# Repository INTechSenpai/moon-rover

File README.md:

# INTech Senpaï vous présente son dernier robot : [le moon rover !](https://intechsenpai.github.io/moon-rover/)

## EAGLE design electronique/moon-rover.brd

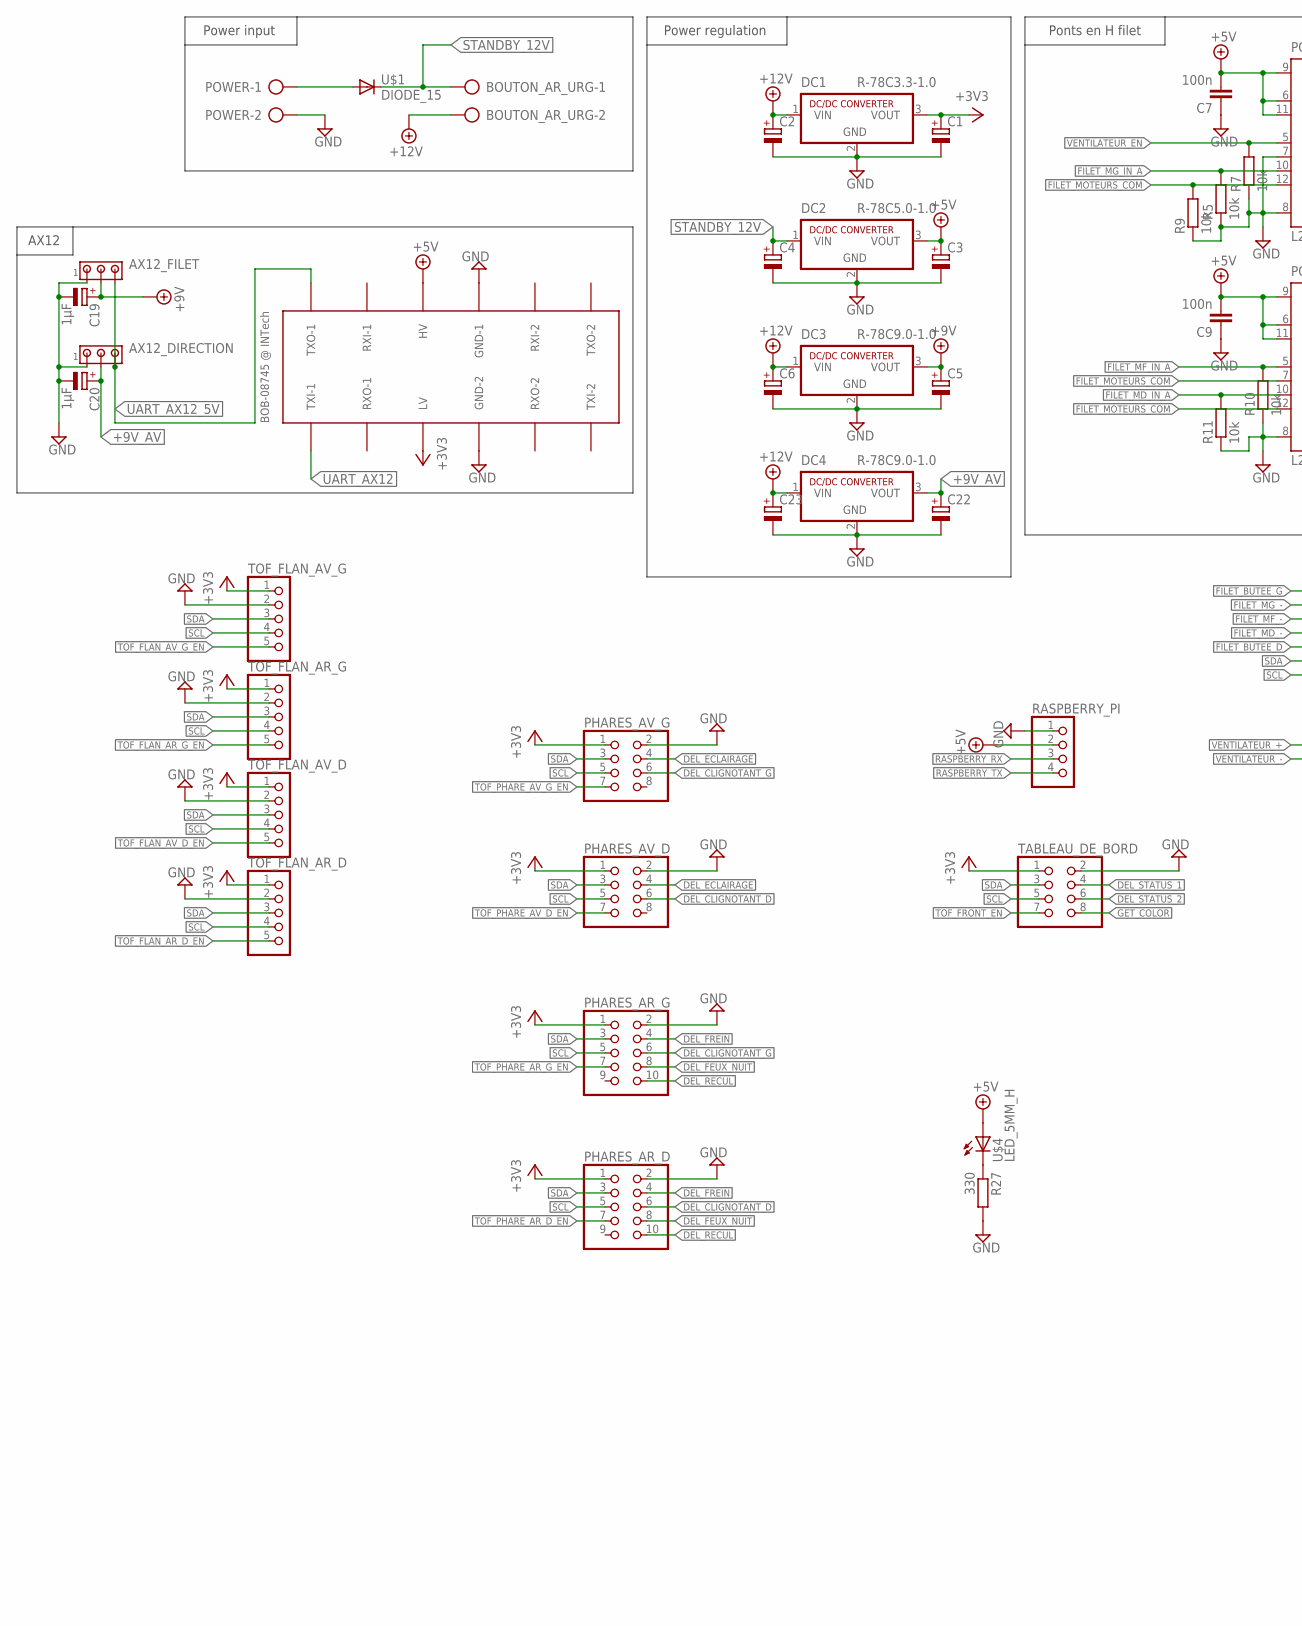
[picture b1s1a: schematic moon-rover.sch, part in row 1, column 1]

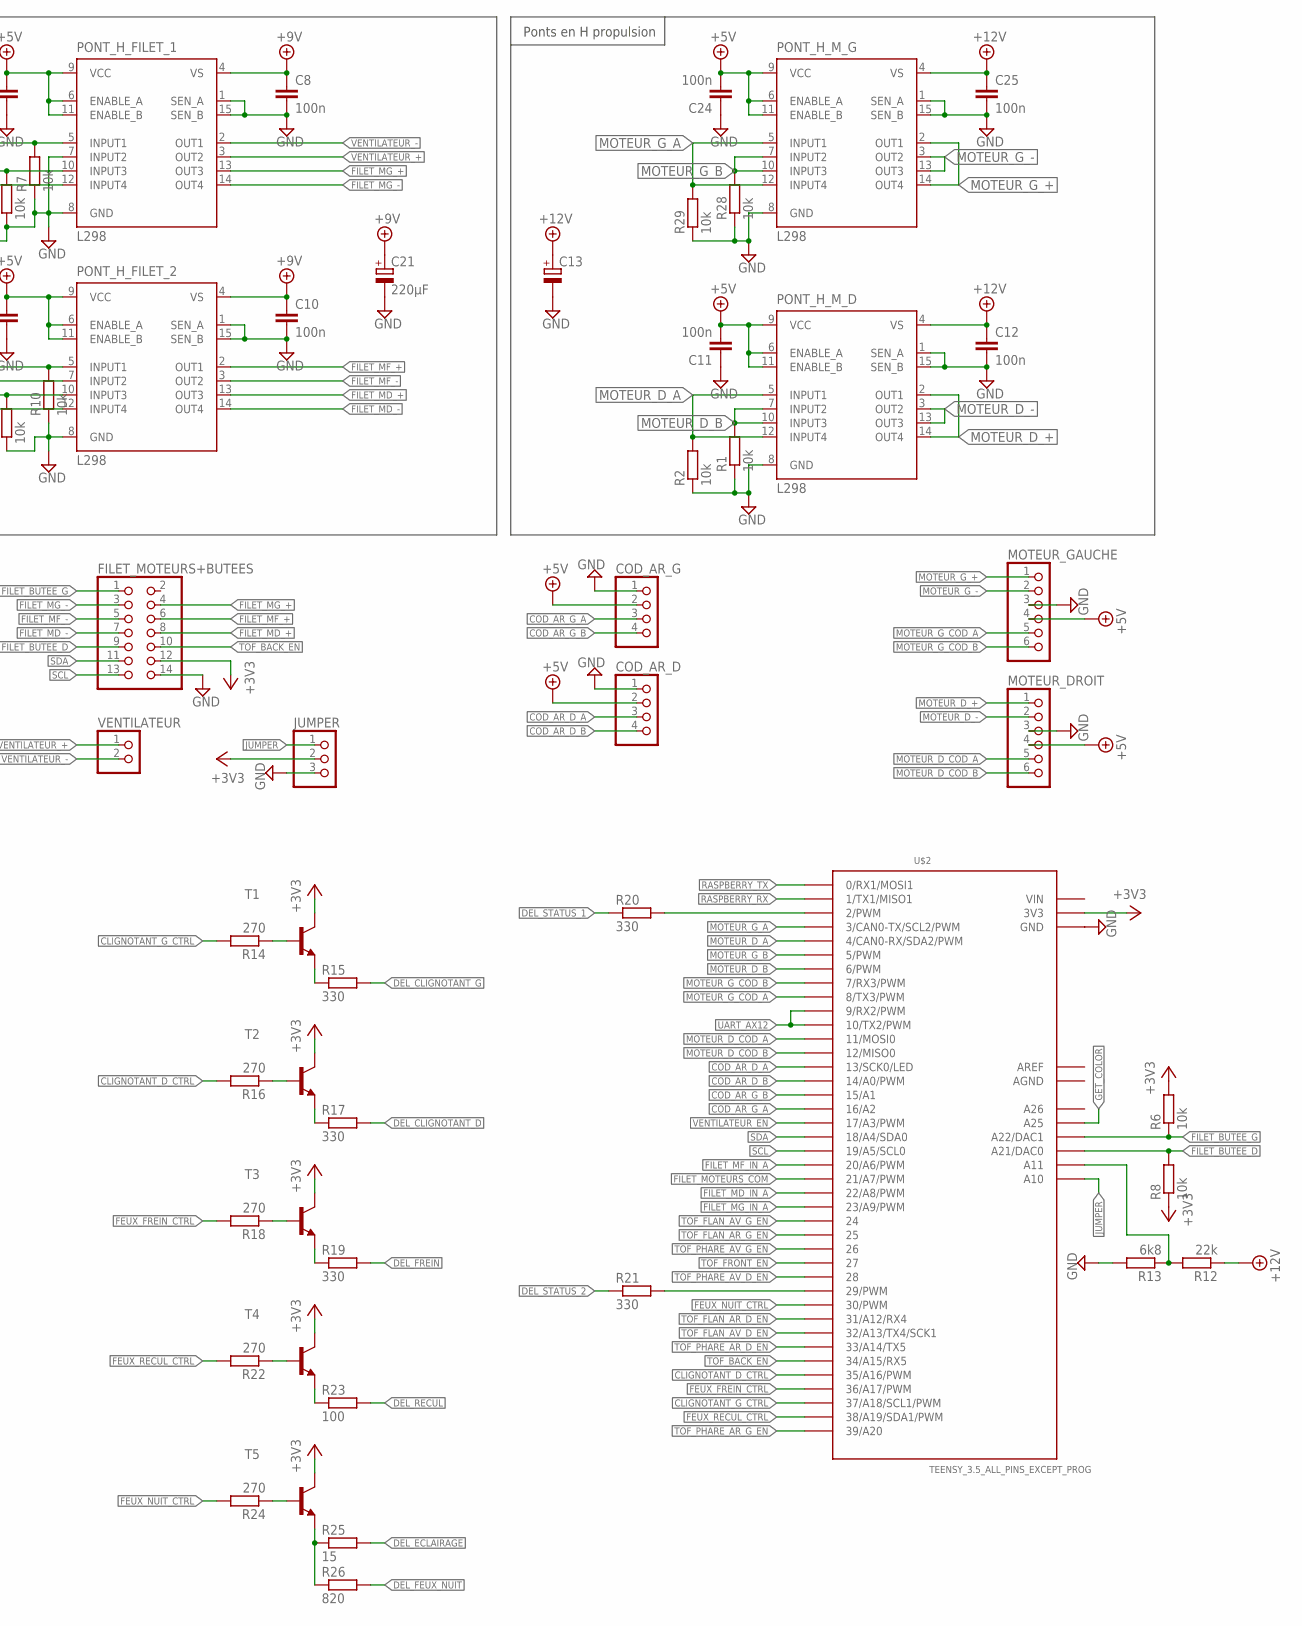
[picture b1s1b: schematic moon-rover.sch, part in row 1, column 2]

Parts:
AX12_DIRECTION, AX12_FILET: MTA03-100; 10X03MTA
BOUTON_AR_URG: AK300/2
C1, C2, C3, C4, C5, C6, C22, C23: CPOL-EUE2.5-6; E2,5-6
C7, C8, C9, C10, C11, C12, C24, C25: 100n; C050-024X044
C13: CPOL-EUE5-13; E5-13
C19, C20: 1µF; E2,5-5
C21: 220µF; E3,5-8
COD_AR_D: PINHD-1X4/90; 1X04/90
COD_AR_G: PINHD-1X4/90; 1X04/90
DC1: R-78C3.3-1.0; SIP3
DC2: R-78C5.0-1.0; SIP3
DC3, DC4: R-78C9.0-1.0; SIP3
FILET_MOTEURS+BUTEES: PINHD-2X7; 2X07
JUMPER: PINHD-1X3/90; 1X03/90
MOTEUR_DROIT: PINHD-1X6/90; 1X06/90
MOTEUR_GAUCHE: PINHD-1X6/90; 1X06/90
PHARES_AR_D: PINHD-2X5; 2X05
PHARES_AR_G: PINHD-2X5; 2X05
PHARES_AV_D: PINHD-2X4; 2X04
PHARES_AV_G: PINHD-2X4; 2X04
PONT_H_FILET_1, PONT_H_FILET_2: L298; MULTIWATT-15
PONT_H_M_D: L298; MULTIWATT-15; MPN L298N
PONT_H_M_G: L298; MULTIWATT-15; MPN L298N
POWER: AK300/2
R1, R2, R5, R6, R7, R8, R9, R10, R11, R28, R29: 10k; 0204/7
R12: 22k; 0204/7
R13: 6k8; 0204/7
R14, R16, R18, R22: 270; 0204/7
R15, R17, R19, R21: 330; 0207/2V
R20, R27: 330; 0204/7
R23: 100; 0207/2V
R24: 270; 0207/2V
R25: 15; 0207/2V
R26: 820; 0207/2V
RASPBERRY_PI: PINHD-1X4/90; 1X04/90
T1, T2, T3, T4, T5: BC237-NPN-TO92-CBE; TO92-CBE
TABLEAU_DE_BORD: PINHD-2X4; 2X04
TOF_FLAN_AR_D: PINHD-1X5; 1X05
TOF_FLAN_AR_G: PINHD-1X5; 1X05
TOF_FLAN_AV_D: PINHD-1X5; 1X05
TOF_FLAN_AV_G: PINHD-1X5; 1X05
U$1: DIODE_15; DO201-15
U$2: TEENSY_3.5_ALL_PINS_EXCEPT_PROG
U$3: BOB-08745
U$4: LED_5MM_H; Q62902-B155
VENTILATEUR: PINHD-1X2/90; 1X02/90

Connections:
+3V3: C1.+, DC1.3 (VOUT), FILET_MOTEURS+BUTEES.12, JUMPER.2, PHARES_AR_D.1, PHARES_AR_G.1, PHARES_AV_D.1, PHARES_AV_G.1, R6.2, R8.1, T1.C, T2.C, T3.C, T4.C, T5.C, TABLEAU_DE_BORD.1, TOF_FLAN_AR_D.1, TOF_FLAN_AR_G.1, TOF_FLAN_AV_D.1, TOF_FLAN_AV_G.1, U$2.3.3V (3V3), U$2.3.3V3 (3V3), U$3.LV
+5V: C3.+, C7.2, C9.2, C11.2, C24.2, COD_AR_D.2, COD_AR_G.2, DC2.3 (VOUT), MOTEUR_DROIT.4, MOTEUR_GAUCHE.4, PONT_H_FILET_1.6 (ENABLE_A), PONT_H_FILET_1.9 (VCC), PONT_H_FILET_1.11 (ENABLE_B), PONT_H_FILET_2.6 (ENABLE_A), PONT_H_FILET_2.9 (VCC), PONT_H_FILET_2.11 (ENABLE_B), PONT_H_M_D.6 (ENABLE_A), PONT_H_M_D.9 (VCC), PONT_H_M_D.11 (ENABLE_B), PONT_H_M_G.6 (ENABLE_A), PONT_H_M_G.9 (VCC), PONT_H_M_G.11 (ENABLE_B), RASPBERRY_PI.2, U$3.HV, U$4.A+
+9V: AX12_FILET.2, C5.+, C8.1, C10.1, C19.+, C21.+, DC3.3 (VOUT), PONT_H_FILET_1.4 (VS), PONT_H_FILET_2.4 (VS)
+9V_AV: AX12_DIRECTION.2, C20.+, C22.+, DC4.3 (VOUT)
+12V: BOUTON_AR_URG.2, C2.+, C6.+, C12.1, C13.+, C23.+, C25.1, DC1.1 (VIN), DC3.1 (VIN), DC4.1 (VIN), PONT_H_M_D.4 (VS), PONT_H_M_G.4 (VS), R12.1
AGND: U$2.AGND
AREF: U$2.AREF
CLIGNOTANT_D_CTRL: R16.2, U$2.35/A16 (35/A16/PWM)
CLIGNOTANT_G_CTRL: R14.2, U$2.37/A18 (37/A18/SCL1/PWM)
COD_AR_D_A: COD_AR_D.3, U$2.13 (13/SCK0/LED)
COD_AR_D_B: COD_AR_D.4, U$2.14/A0 (14/A0/PWM)
COD_AR_G_A: COD_AR_G.3, U$2.16/A2
COD_AR_G_B: COD_AR_G.4, U$2.15/A1
DEL_CLIGNOTANT_D: PHARES_AR_D.6, PHARES_AV_D.6, R17.2
DEL_CLIGNOTANT_G: PHARES_AR_G.6, PHARES_AV_G.6, R15.2
DEL_ECLAIRAGE: PHARES_AV_D.4, PHARES_AV_G.4, R25.2
DEL_FEUX_NUIT: PHARES_AR_D.8, PHARES_AR_G.8, R26.2
DEL_FREIN: PHARES_AR_D.4, PHARES_AR_G.4, R19.2
DEL_RECUL: PHARES_AR_D.10, PHARES_AR_G.10, R23.2
DEL_STATUS_1: R20.1, TABLEAU_DE_BORD.4
DEL_STATUS_2: R21.1, TABLEAU_DE_BORD.6
FEUX_FREIN_CTRL: R18.2, U$2.36/A17 (36/A17/PWM)
FEUX_NUIT_CTRL: R24.2, U$2.30 (30/PWM)
FEUX_RECUL_CTRL: R22.2, U$2.38/A19 (38/A19/SDA1/PWM)
FILET_BUTEE_D: FILET_MOTEURS+BUTEES.9, R8.2, U$2.A21 (A21/DAC0)
FILET_BUTEE_G: FILET_MOTEURS+BUTEES.1, R6.1, U$2.A22 (A22/DAC1)
FILET_MD_+: FILET_MOTEURS+BUTEES.8, PONT_H_FILET_2.13 (OUT3)
FILET_MD_-: FILET_MOTEURS+BUTEES.7, PONT_H_FILET_2.14 (OUT4)
FILET_MD_IN_A: PONT_H_FILET_2.10 (INPUT3), R11.2, U$2.22/A8 (22/A8/PWM)
FILET_MF_+: FILET_MOTEURS+BUTEES.6, PONT_H_FILET_2.2 (OUT1)
FILET_MF_-: FILET_MOTEURS+BUTEES.5, PONT_H_FILET_2.3 (OUT2)
FILET_MF_IN_A: PONT_H_FILET_2.5 (INPUT1), R10.2, U$2.20/A6 (20/A6/PWM)
FILET_MG_+: FILET_MOTEURS+BUTEES.4, PONT_H_FILET_1.13 (OUT3)
FILET_MG_-: FILET_MOTEURS+BUTEES.3, PONT_H_FILET_1.14 (OUT4)
FILET_MG_IN_A: PONT_H_FILET_1.10 (INPUT3), R5.2, U$2.23/A9 (23/A9/PWM)
FILET_MOTEURS_COM: PONT_H_FILET_1.12 (INPUT4), PONT_H_FILET_2.7 (INPUT2), PONT_H_FILET_2.12 (INPUT4), R9.2, U$2.21/A7 (21/A7/PWM)
GET_COLOR: TABLEAU_DE_BORD.8, U$2.A25
GND: AX12_DIRECTION.1, AX12_FILET.1, C1.-, C2.-, C3.-, C4.-, C5.-, C6.-, C7.1, C8.2, C9.1, C10.2, C11.1, C12.2, C13.-, C19.-, C20.-, C21.-, C22.-, C23.-, C24.1, C25.2, COD_AR_D.1, COD_AR_G.1, DC1.2 (GND), DC2.2 (GND), DC3.2 (GND), DC4.2 (GND), FILET_MOTEURS+BUTEES.14, JUMPER.3, MOTEUR_DROIT.3, MOTEUR_GAUCHE.3, PHARES_AR_D.2, PHARES_AR_G.2, PHARES_AV_D.2, PHARES_AV_G.2, PONT_H_FILET_1.1 (SEN_A), PONT_H_FILET_1.7 (INPUT2), PONT_H_FILET_1.8 (GND), PONT_H_FILET_1.15 (SEN_B), PONT_H_FILET_2.1 (SEN_A), PONT_H_FILET_2.8 (GND), PONT_H_FILET_2.15 (SEN_B), PONT_H_M_D.1 (SEN_A), PONT_H_M_D.8 (GND), PONT_H_M_D.15 (SEN_B), PONT_H_M_G.1 (SEN_A), PONT_H_M_G.8 (GND), PONT_H_M_G.15 (SEN_B), POWER.2, R1.1, R2.1, R5.1, R7.1, R9.1, R10.1, R11.1, R13.2, R27.2, R28.1, R29.1, RASPBERRY_PI.1, TABLEAU_DE_BORD.2, TOF_FLAN_AR_D.2, TOF_FLAN_AR_G.2, TOF_FLAN_AV_D.2, TOF_FLAN_AV_G.2, U$2.GND, U$2.GND1 (GND), U$2.GND3 (GND), U$2.GND4 (GND), U$3.GND-1, U$3.GND-2
JUMPER: JUMPER.1, U$2.A10
MOTEUR_D_+: MOTEUR_DROIT.1, PONT_H_M_D.2 (OUT1), PONT_H_M_D.14 (OUT4)
MOTEUR_D_-: MOTEUR_DROIT.2, PONT_H_M_D.3 (OUT2), PONT_H_M_D.13 (OUT3)
MOTEUR_D_A: PONT_H_M_D.5 (INPUT1), PONT_H_M_D.12 (INPUT4), R2.2, U$2.4 (4/CAN0-RX/SDA2/PWM)
MOTEUR_D_B: PONT_H_M_D.7 (INPUT2), PONT_H_M_D.10 (INPUT3), R1.2, U$2.6 (6/PWM)
MOTEUR_D_COD_A: MOTEUR_DROIT.5, U$2.11 (11/MOSI0)
MOTEUR_D_COD_B: MOTEUR_DROIT.6, U$2.12 (12/MISO0)
MOTEUR_G_+: MOTEUR_GAUCHE.1, PONT_H_M_G.2 (OUT1), PONT_H_M_G.14 (OUT4)
MOTEUR_G_-: MOTEUR_GAUCHE.2, PONT_H_M_G.3 (OUT2), PONT_H_M_G.13 (OUT3)
MOTEUR_G_A: PONT_H_M_G.5 (INPUT1), PONT_H_M_G.12 (INPUT4), R29.2, U$2.3 (3/CAN0-TX/SCL2/PWM)
MOTEUR_G_B: PONT_H_M_G.7 (INPUT2), PONT_H_M_G.10 (INPUT3), R28.2, U$2.5 (5/PWM)
MOTEUR_G_COD_A: MOTEUR_GAUCHE.5, U$2.8 (8/TX3/PWM)
MOTEUR_G_COD_B: MOTEUR_GAUCHE.6, U$2.7 (7/RX3/PWM)
unnamed: R14.1, T1.B
unnamed: R12.2, R13.1, U$2.A11
unnamed: R15.1, T1.E
unnamed: R27.1, U$4.K- (C-)
unnamed: POWER.1, U$1.A (A+)
unnamed: R16.1, T2.B
unnamed: R17.1, T2.E
unnamed: R18.1, T3.B
unnamed: R19.1, T3.E
unnamed: R20.2, U$2.2 (2/PWM)
unnamed: R21.2, U$2.29 (29/PWM)
unnamed: R22.1, T4.B
unnamed: R23.1, T4.E
unnamed: R24.1, T5.B
unnamed: R25.1, R26.1, T5.E
RASPBERRY_RX: RASPBERRY_PI.3, U$2.1 (1/TX1/MISO1)
RASPBERRY_TX: RASPBERRY_PI.4, U$2.0 (0/RX1/MOSI1)
SCL: FILET_MOTEURS+BUTEES.13, PHARES_AR_D.5, PHARES_AR_G.5, PHARES_AV_D.5, PHARES_AV_G.5, TABLEAU_DE_BORD.5, TOF_FLAN_AR_D.4, TOF_FLAN_AR_G.4, TOF_FLAN_AV_D.4, TOF_FLAN_AV_G.4, U$2.19/A5 (19/A5/SCL0)
SDA: FILET_MOTEURS+BUTEES.11, PHARES_AR_D.3, PHARES_AR_G.3, PHARES_AV_D.3, PHARES_AV_G.3, TABLEAU_DE_BORD.3, TOF_FLAN_AR_D.3, TOF_FLAN_AR_G.3, TOF_FLAN_AV_D.3, TOF_FLAN_AV_G.3, U$2.18/A4 (18/A4/SDA0)
STANDBY_12V: BOUTON_AR_URG.1, C4.+, DC2.1 (VIN), U$1.C (C-)
TOF_BACK_EN: FILET_MOTEURS+BUTEES.10, U$2.34/A15 (34/A15/RX5)
TOF_FLAN_AR_D_EN: TOF_FLAN_AR_D.5, U$2.31/A12 (31/A12/RX4)
TOF_FLAN_AR_G_EN: TOF_FLAN_AR_G.5, U$2.25
TOF_FLAN_AV_D_EN: TOF_FLAN_AV_D.5, U$2.32/A13 (32/A13/TX4/SCK1)
TOF_FLAN_AV_G_EN: TOF_FLAN_AV_G.5, U$2.24
TOF_FRONT_EN: TABLEAU_DE_BORD.7, U$2.27
TOF_PHARE_AR_D_EN: PHARES_AR_D.7, U$2.33/A14 (33/A14/TX5)
TOF_PHARE_AR_G_EN: PHARES_AR_G.7, U$2.39/A20
TOF_PHARE_AV_D_EN: PHARES_AV_D.7, U$2.28
TOF_PHARE_AV_G_EN: PHARES_AV_G.7, U$2.26
UART_AX12: U$2.9 (9/RX2/PWM), U$2.10 (10/TX2/PWM), U$3.TXI-1
UART_AX12_5V: AX12_DIRECTION.3, AX12_FILET.3, U$3.TXO-1
VENTILATEUR_+: PONT_H_FILET_1.3 (OUT2), VENTILATEUR.1
VENTILATEUR_-: PONT_H_FILET_1.2 (OUT1), VENTILATEUR.2
VENTILATEUR_EN: PONT_H_FILET_1.5 (INPUT1), R7.2, U$2.17/A3 (17/A3/PWM)
VIN: U$2.VIN

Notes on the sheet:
Power regulation
Ponts en H filet
Power input
Ponts en H propulsion
AX12

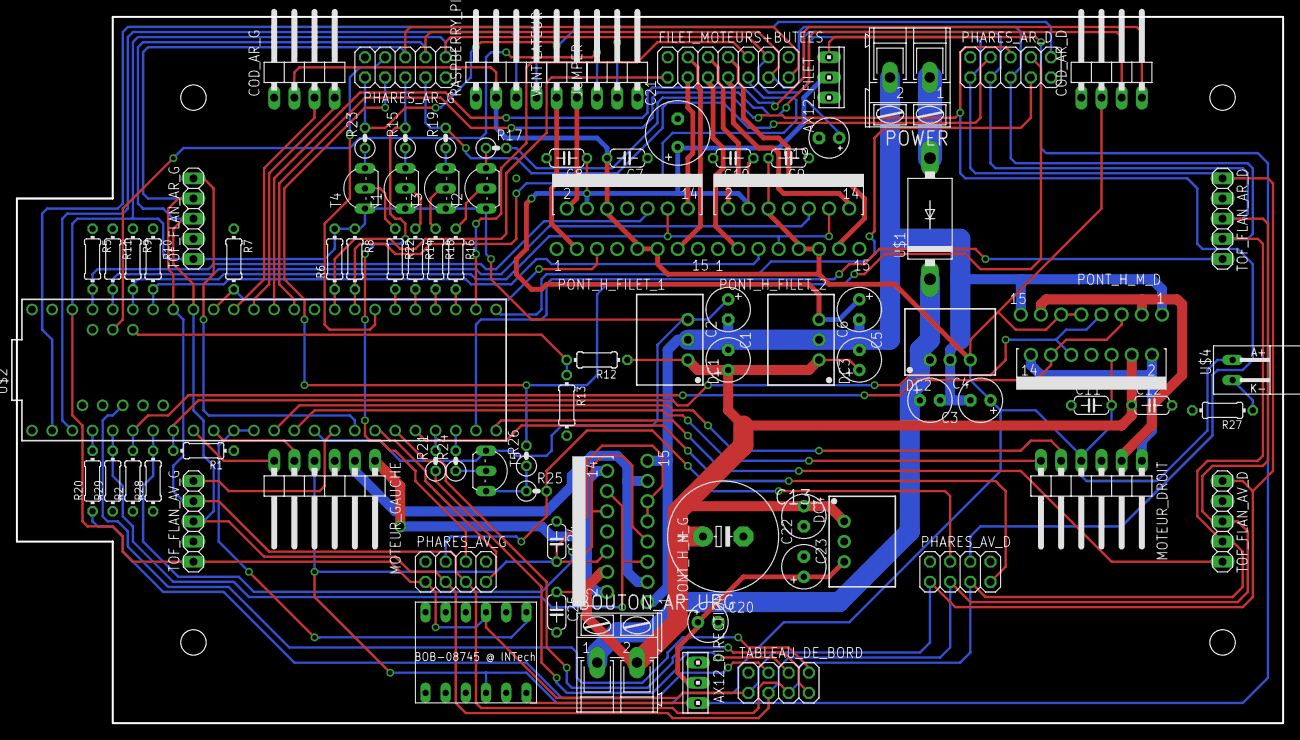
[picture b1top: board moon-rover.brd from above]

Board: 2 copper layers, 159.4 x 88.9 mm, 85 parts (0 on the bottom side), 84 nets.

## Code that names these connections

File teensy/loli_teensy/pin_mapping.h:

#ifndef _PIN_MAPPING_h
#define _PIN_MAPPING_h

/* Encodeurs arrières */
#define PIN_A_RIGHT_BACK_ENCODER	13
#define PIN_B_RIGHT_BACK_ENCODER	14
#define PIN_B_LEFT_BACK_ENCODER		15
#define PIN_A_LEFT_BACK_ENCODER		16


/* Encodeurs des moteurs de propultion */
#define PIN_B_LEFT_MOTOR_ENCODER	7
#define PIN_A_LEFT_MOTOR_ENCODER	8
#define PIN_A_RIGHT_MOTOR_ENCODER	11
#define PIN_B_RIGHT_MOTOR_ENCODER	12


/* Ponts en H des moteurs de propultion */
#define PIN_DIRECTION_LEFT_MOTOR	3
#define PIN_DIRECTION_RIGHT_MOTOR	4
#define PIN_PWM_LEFT_MOTOR			5
#define PIN_PWM_RIGHT_MOTOR			6


/* Ponts en H des moteurs du filet */
#define PIN_VENTILATEUR		17
#define PIN_MOTOR_NET		20
#define PIN_RIGHT_MOTOR_NET	22
#define PIN_LEFT_MOTOR_NET	23
#define PIN_NET_COM			21

/* Capteurs fin de course du filet */
#if defined(__MK64FX512__) || defined(__MK66FX1M0__) // Teensy 3.5 ou 3.6
#define PIN_BUTEE_G			A22
#define PIN_BUTEE_D			A21
#elif defined(__MK20DX128__) || defined(__MK20DX256__) // Teensy 3.0 3.1 ou 3.2
#define PIN_BUTEE_G			67
#define PIN_BUTEE_D			66
#endif


/* Capteurs ToF : pin 'enable' */
#define PIN_TOF_FLAN_AV_G	24
#define PIN_TOF_FLAN_AR_G	25
#define PIN_TOF_PHARE_AV_G	26
#define PIN_TOF_FRONT		27
#define PIN_TOF_PHARE_AV_D	28
#define PIN_TOF_FLAN_AR_D	31
#define PIN_TOF_FLAN_AV_D	32
#define PIN_TOF_PHARE_AR_D	33
#define PIN_TOF_BACK		34
#define PIN_TOF_PHARE_AR_G	39


/* DELs */
#define PIN_DEL_STATUS_1	2
#define PIN_DEL_STATUS_2	29
#define PIN_FEUX_NUIT		30
#define PIN_CLIGNOTANT_D	35
#define PIN_FEUX_FREIN		36
#define PIN_CLIGNOTANT_G	37
#define PIN_FEUX_RECUL		38


/* Divers capteurs */
#if defined(__MK64FX512__) || defined(__MK66FX1M0__) // Teensy 3.5 ou 3.6
#define PIN_GET_COLOR		A25
#elif defined(__MK20DX128__) || defined(__MK20DX256__) // Teensy 3.0 3.1 ou 3.2
#define PIN_GET_COLOR		68
#endif
#define PIN_GET_VOLTAGE		A11
#define PIN_GET_JUMPER		A10


#endif

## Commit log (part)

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2017-05-14 Marge plus stricte pour la replanif
2017-05-14 Bugfix SetVitesse
2017-05-14 Ajout ordre LL SetDirection + nouveau cas d'erreur pour FollowTrajectory
2017-05-15 Intégration de FAR_AWAY
2017-05-15 Intégration de SET_DIRECTION
2017-05-15 Bugfix iterator
2017-05-15 Bugfix récupération de la cinématique du robot
2017-05-15 Scan (WIP)
2017-05-15 Formatage du code source
2017-05-15 Initialisation du PF aussi quand on retente
2017-05-15 1e version du scan
2017-05-15 Bugfix scan
2017-05-15 Couleur SCAN
2017-05-15 Intégration de la bascule comme obstacle visible
2017-05-15 Bugfix série : on renvoie un END_ORDER si demandé
2017-05-16 Scan attend la réponse des AX-12
2017-05-16 Concurrent collections
2017-05-16 Tests
2017-05-16 Bugfix tests
2017-05-16 ajout ordre Scann
2017-05-16 Test unitaire
2017-05-16 Verbose
2017-05-16 Mise à jour du protocole du scan
2017-05-16 scann plus rapide
2017-05-16 Test de correction d'odo
2017-05-16 Travis vérifie les tests unitaires
2017-05-16 Bugfix gestion code de retour actionneurs
2017-05-16 Verbose correction
2017-05-16 Warnings
2017-05-16 Du ménage dans les tests
2017-05-16 Ajout du test test_arc_cercle
2017-05-16 Bugfix correction
2017-05-17 Bugfix affichage orientation roues + capteurs
2017-05-17 On vérifie que le robot est bien arrivé à destination
2017-05-17 Vérification de l'arrivée
2017-05-17 On vérifie que le scan est nécessaire
2017-05-17 Gestion de l'état du filet
2017-05-17 Page GitHub
2017-05-17 ajout ordre closeNetForce
2017-05-17 bugfix ax12 + ajout mediane IR
2017-05-17 Set theme jekyll-theme-minimal
2017-05-17 Ajout d'une photo de l'élec
2017-05-17 maj script : closeNetForce à la place de closeNet à un endroit
2017-05-17 Mise à jour page github
2017-05-17 Poster
2017-05-17 scripts d'automatisation : gestion version python
2017-05-17 scripts d'automatisation : encore plus de compatibilité
2017-05-17 Code bas niveau compatible linux et ArduinoIDE
2017-05-17 Ajout de CloseNetForce
2017-05-17 Option de verbose dans VideoReader
2017-05-17 Maj gitignore pour vscode
2017-05-17 Frame-to-frame + désactivation des sprites
2017-05-17 Test capteurs
2017-05-17 Ajout de l'angle des roues dans la vidéo
2017-05-17 Bugfix
2017-05-17 Envoi des angles des roues du robot
2017-05-17 VideoReader
2017-05-18 Verbose d'arrivée sur cratère
2017-05-18 Affichage du vecteur de direction
2017-05-18 Envoi périodique de ping + arrêt automatique si pas de données du LL pendant 3s
2017-05-18 Démarrage automatique du HL, code d'erreur et reboot
2017-05-18 Timeout LL : 2s et pas 3
2017-05-19 Arrêt des threads
2017-05-19 Génération de gif depuis VideoReader directement
2017-05-19 Arrêt des threads, suite
2017-05-19 Le ToF long arrière ne sert plus de jauge
2017-05-19 Fix capteur ToF LP arriere
2017-05-19 Site du projet
2017-05-19 Hack pour ne pas mettre d'obstacle d'ennemi dans la zone de départ
2017-05-19 Bugfix affichage vecteur
2017-05-19 Gestion de l'arrêt du code HL + code d'erreur
2017-05-19 Test supplémentaire
2017-05-19 Zoom
2017-05-19 Bugfix IteratorCheminPathfiniding
2017-05-19 Affichage de la trajectoire théorique parcourue
2017-05-19 Bugfix PF
2017-05-20 console de debug LL embarquée sur rpi
2017-05-21 Timeout sur l'attente de réponse au STOP
2017-05-21 Simplification code
2017-05-21 Bornes distance/orientation pour prendre les cratères
2017-05-21 Bugfix replanification
2017-05-21 MàJ graphe des dépendances
2017-05-21 Scripts symétrisés
2017-05-21 Petit oubli
2017-05-21 Couleur du vecteur
2017-05-21 Fichiers last.txt et last.vid
2017-05-21 Suppression des last.txt et last.vid au début du code
2017-05-21 Pas .vid mais .dat
2017-05-21 Bugfix fin de test
2017-05-21 maj shell script getLog
2017-05-21 Bugfix tests unitaires
2017-05-21 Arrêt HL au bout d'une seconde
2017-05-21 Test avance 2cm
2017-05-21 Chemin considéré comme vide au démarrage
2017-05-21 Bugfix LL timeout
2017-05-21 Droits +x pour serial.sh
2017-05-21 Bugfix follow trajectory
2017-05-21 Affichage des trames non finies à la fin
2017-05-21 maj script serial (exp)
2017-05-21 maj battery sensor + calibration
2017-05-21 Bugfix fermeture série
2017-05-21 script serial maj exp
2017-05-21 script serial maj exp2
2017-05-21 Trajectoire de correction jusqu'à cratère
2017-05-21 Bugfix màj chemin
2017-05-21 Bugfix typo
2017-05-21 Ping régulier moins con
2017-05-22 LL verbose
2017-05-22 Verbose destructor de container
2017-05-22 Ajout de ClosedSerialException
2017-05-22 Angles d'attaque permis sur le cratère
2017-05-22 Bugfix angles d'attaque permis
2017-05-22 Bugfix cratère
2017-05-22 Performances PF
2017-05-22 Le recalage sur le cratère est maintenant géré par le script lui-même
2017-05-22 Plus de vérifications et d'essais
2017-05-22 Bugfix replanif
2017-05-22 MàJ angles d'attaque des cratères du haut
2017-05-22 Paths
2017-05-22 Bugfix test
2017-05-22 FPS max pour la vidéo
2017-05-22 Hm… non
2017-05-22 Suppression du LL_TIMEOUT
2017-05-22 Bascule !
2017-05-22 Bugfix avance
2017-05-22 Script dépose
2017-05-22 Bugfix update cinématique
2017-05-22 Les scripts ne sont plus forcément liés à des cercles
2017-05-22 Script
2017-05-23 Bugfix symétrie
2017-05-23 Marge des cercles
2017-05-23 Bugfix scripts
2017-05-23 Volatile dans Cercle
2017-05-23 Test dépose balles juste après cratère
2017-05-23 Homolo
2017-05-23 Homolo avec funny action
2017-05-23 ant build
2017-05-23 Suppression verrou série
2017-05-23 Test depose
2017-05-23 Angles autorisés dépose
2017-05-23 Bugfix critique CinematiqueObs
2017-05-23 Gestion symétrie
2017-05-23 Symétrie
2017-05-23 Bugfix vidéo
2017-05-23 Pas de vérif d'angle d'attaque sur l'asser
2017-05-23 Bugfix désactivation obstacles
2017-05-23 Bugfix script dépose
2017-05-23 Prise + dépose
2017-05-23 Code de match
2017-05-23 Calcul du premier chemin avant le jumper
2017-05-23 Arrêt propre hors des tests
2017-05-23 On ne vire plus les cylindres pris par un ennemi
2017-05-23 Bugfix couleur
2017-05-23 run.sh
2017-05-23 Petit changement archi pour "avance"
2017-05-23 CloseNet tout seul
2017-05-23 Config par défaut
2017-05-23 Protocole pré-match
2017-05-23 Prématch
2017-05-23 Bugfix dégueulasse
2017-05-23 Script match
2017-05-23 Script match encore
2017-05-23 Pas de funny action pendant les tests
2017-05-23 Config dynamique propre
2017-05-23 Script cratère
2017-05-23 Plus de Strategie.java
2017-05-23 Archi script
2017-05-23 Primitives de déplacement courbe dans Robot
2017-05-23 Arrivée sur cercle
2017-05-23 Vitesse script
2017-05-23 Hack dégueu
2017-05-23 Hack dégueu 2
2017-05-23 Hack dégueu 3
2017-05-23 Depose
2017-05-23 Config correction + on utilise uniquement du mur du haut
2017-05-23 LL verbose + loli
2017-05-23 Tests unitaires
2017-05-23 Sleep demande couleur
2017-05-23 Changement protocole envoi de XYO
2017-05-24 Config correction
2017-05-24 verbos + GROS CHANGEMENT de protocole pour l'écriture des positions: y est aussi translaté
2017-05-24 Bugfix protocole
2017-05-24 Ceci, curieusement, n'est pas un hack à proprement parler
2017-05-24 Correction
2017-05-24 La funny action est faite par le LL
2017-05-24 Funny action à la fin du MatchChrono, dans le LL
2017-05-24 Match court
2017-05-24 On ne prend pas les gros cratères
2017-05-24 Do a barrel roll !
2017-05-24 Test sans robot
2017-05-24 Bugfix script
2017-05-24 Revert "Primitives de déplacement courbe dans Robot"
    This reverts commit e9819e085910dcbbc0d5cb0d087ab82d3991df3d.
2017-05-24 Sir, sir, j'ai trouvé !
2017-05-24 Bugfix arrêt
2017-05-24 MOUAHAHAHA
2017-05-24 Config timeout PF
2017-05-24 C'est plus facile d'écrire des matchs
2017-05-24 Calcul de PF en avance
2017-05-24 Match fiable
2017-05-24 Affichage cercle
2017-05-24 Ressort de la zone de dépose
2017-05-24 Scripts
2017-05-24 Avec le fichier…
2017-05-24 Correction sur le mur du bas aussi
2017-05-24 Script cratère plus fiable ?
2017-05-24 Script cratère plus fiable 2
2017-05-24 Script cratère plus fiable 3
2017-05-24 Jumper
2017-05-24 Attente fermeture conversations moindre
2017-05-24 changement startup procedure, plus safe
2017-05-24 Sécu LL: on stoppe le robot à la fin du match car le HL est trop gogol pour se rendre compte qu'on a fini
2017-05-25 Réutilisation de chemins entre match
2017-05-25 Bugfix enregistrement chemins
2017-05-25 Chemins
2017-05-25 Démo heptacle
2017-05-25 Bugfix démo
2017-05-25 Bugfix démo 2
2017-05-25 Nb essais PF très grand
2017-05-25 Ferme filet non bloquant à la fin de la dépose
2017-05-25 LL: ouverture du filet avant la fin du match, au cas où il soit rempli
2017-05-26 Bugfix memory manager
2017-05-27 Bugfix contrôle
2017-05-27 ajout fonctionnalitées télécommande LL
2017-05-27 Contrôle à distance
2017-05-27 Sleep arrêt contrôle
2017-05-27 LL: bugfix SetDirection
2017-05-27 Avec tous les fichiers
2017-05-27 Proto contrôle à distance
2017-05-27 Interface client de contrôle finie
2017-05-27 Client graphique
2017-05-27 Serveur de contrôle à distance
2017-05-27 Client contrôle à distance sans container
2017-05-27 LL debug ordres de télécommande
2017-05-27 Courbure max
2017-05-27 ajout image bg remote control
2017-05-27 schéma de clignottement différent pour reconnaitre la branche expérimentale
2017-05-27 Config keybindings
2017-05-27 maj doc pour fonctions télécommande
2017-05-27 Bugfix tourner
2017-05-27 Config pour télécommande
2017-05-27 Télécommande : pouvoir tourner
2017-05-27 On ralentit plus vite qu'on accélère
2017-05-27 Reset vitesse après arrêt LL
2017-05-27 Multitouches
2017-05-27 Doc key codes
2017-05-27 Bugfix multitouches
2017-05-27 Accélération télécommande + bugfix vitesse
2017-05-27 Ajustement vitesse rotation
2017-05-27 déplacement images bg
2017-05-27 Augmentation débit connexion
2017-05-27 Ordres actionneurs
2017-05-27 Vitesse rotation
2017-05-27 Commandes actionneurs par télécommandes
2017-05-27 Image
2017-05-27 README
2017-05-28 Site github
2017-05-29 réasservissement AX12 filet
2017-06-01 Photo rover + prix
2017-06-03 ajout script python pour commande par wiimote
2017-06-03 correction timeout comm ax12
2017-06-03 add python2 script
2017-06-03 maj script python wiimote
2017-06-03 mapping boutons wiimote
2017-06-04 wiimote: ajout gestion accéléromètre + joystick
2017-06-05 Portabilité du serveur de contrôle + nouveaux ordres
2017-06-05 Le client télécommande java se reconnecte automatique au serveur
2017-06-05 Client télécommande python (WIP)
2017-06-05 Bugfix python
2017-06-05 maj .gitignore pour dev python
2017-06-05 c'est parti pour un test
2017-06-05 le HL est FOUUUUU ! :p
2017-06-05 Retrait de la fonctionnalité anti-désasservissement de l'ax12 du filet
2017-06-05 Protocole python : ajout de ping, speed_up, speed_down, turn_left, turn_right, reset_wheels
2017-06-05 Bugfix serveur télécommande
2017-06-05 add verbose
2017-06-05 Shutdown du serveur stop le rover
2017-06-05 abwabwa
2017-06-05 Bugfix valeurs négatives
2017-06-05 gestion bornes dir et speed
2017-06-05 Java shutdown
2017-06-05 Lecture d'InputStream du socket
2017-06-05 gubfix direction erratique au démarrage
2017-06-05 Bugfix setSpeed
2017-06-05 tentative de filtrage des valeurs de l'accéléromètre
2017-06-05 bugfix direction, les float c'est mal
2017-06-05 ajustement
2017-06-05 le python lance le java !
2017-06-05 le python lance le java ! abwa
2017-06-05 test
2017-06-05 changement vitesses
2017-06-05 abwa
2017-06-05 wiimote python auto-restart
2017-06-05 little fix auto-restart
2017-06-05 kill c'est mieux que terminate face à ce connard de java !
2017-06-05 allume led wiimote
2017-06-05 mode de control indiqué par les DELs de la wiimote
2017-06-07 freinage d'urgence sur détection d'obstacle en mode télécommandé
2017-09-18 Mise à jour lien vers Kraken
2017-10-28 Bugfix D*
2018-05-08 Lien vers le camion grue
